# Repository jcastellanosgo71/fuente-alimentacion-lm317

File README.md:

# Fuente de Alimentación Lineal Regulable - v1.0

## 📌 Descripción General
Diseño de hardware y PCB para una **Fuente de Alimentación Lineal Regulable v1.0** basada en el regulador lineal ajustable **LM317**. El circuito convierte una entrada de voltaje continuo/alterno en una salida regulada ajustable ($V_{DD}$) mediante potenciómetro manual.

---

## 🛠️ Especificaciones y Funcionamiento
- **Entrada y Rectificación:** Bornera $J_1$ a la entrada con puente rectificador de onda completa (4x diodos 1N4004 $D_1-D_4$).
- **Filtrado Principal:** Capacitores electrolíticos en paralelo ($C_1, C_2$ de $2200\,\mu\text{F} / 50\,\text{V}$) para minimizar el rizado en $V_{CC}$.
- **Regulación y Ajuste:** Regulador lineal LM317 ($U_1$) en encapsulado TO-220, ajustado mediante potenciómetro de $5\,\text{k}\Omega$ ($RV_1$) y resistencia $R_2$.
- **Protección y Estabilidad:** Diodos de protección $D_6, D_7$ (1N4004), capacitor de desacople de ajuste $C_3$ ($33\,\mu\text{F}$) y capacitor de salida $C_4$ ($1\,\mu\text{F}$ Tántalo).
- **Salidas y Monitor:** Bornera principal $J_4$, salidas auxiliares $J_2, J_3$ y LED indicador $D_5$.
- **Diseño PCB:** Placa de 2 capas con plano de masa continuo ($GNDREF$).

---

## 📋 Lista de Componentes (BOM)

| Designador | Cantidad | Componente / Valor | Descripción |
| :--- | :--- | :--- | :--- |
| **U1** | 1 | LM317 | Regulador lineal ajustable (TO-220) |
| **D1, D2, D3, D4, D6, D7** | 6 | 1N4004 | Diodos rectificadores |
| **D5** | 1 | LED | Diodo emisor de luz 5mm |
| **C1, C2** | 2 | $2200\,\mu\text{F} / 50\,\text{V}$ | Condensadores electrolíticos radiales |
| **C3** | 1 | $33\,\mu\text{F} / 25\,\text{V}$ | Condensador electrolítico radial |
| **C4** | 1 | $1\,\mu\text{F} / 25\,\text{V}$ | Condensador de tántalo |
| **R1** | 1 | Resistencia (R) | Resistencia fija Through-Hole (LED indicador) |
| **R2** | 1 | $240\,\Omega$ / ¼ W | Resistencia de programación del LM317 (fija en v2.0) |
| **~~RV1~~** | — | ~~Potenciómetro $5\,\text{k}\Omega$~~ | **Retirado en v2.0** (sustituido por control digital) |
| **J1, J4** | 2 | Bornera 2 pines | Entradas/Salidas principales |
| **J2, J3** | 2 | Pin Header 1x02 | Salidas auxiliares $V_{CC}$ y $V_{DD}$ |
| **U2** | 1 | Opamp MCP6002 (o LM358) | Buffer/amplificador no inversor $G=2.15$ **(v2.0)** |
| **R3** | 1 | $10\,\text{k}\Omega$ / ¼ W | Resistencia del filtro RC **(v2.0)** |
| **C5** | 1 | $10\,\mu\text{F}$ / 16 V | Condensador del filtro RC **(v2.0)** |
| **R4** | 1 | $10\,\text{k}\Omega$ / ¼ W ($R_g$) | Resistencia de la red de ganancia **(v2.0)** |
| **R5** | 1 | $11.5\,\text{k}\Omega$ / ¼ W ($R_f'$) | Resistencia de realimentación de ganancia **(v2.0)** |
| **C6** | 1 | $100\,\text{nF}$ | Desacople de alimentación del opamp **(v2.0)** |
| **J5** | 1 | Pin Header 1x03 | Header de control Arduino: `PWM_IN`, `GND`, `VCC_OPAMP` (desde la placa, **no** del Arduino) **(v2.0)** |
| **HS1** | 1 | Disipador TO-220 $R_{th(SA)}\le 5\,^\circ\text{C/W}$ + pasta térmica | **Disipador por defecto** del LM317 (seguro a $0.5\,\text{A}$) **(v2.0)** |

> 📝 **Nota v2.0:** el potenciómetro $RV_1$ **se retira** y $R_2$ **pasa a valor fijo $240\,\Omega$**. Los componentes marcados **(v2.0)** son la etapa de control digital añadida. Ver [Control Digital v2.0](#-control-digital-v20).

---

## 🤖 Control Digital v2.0
En la **v2.0** se elimina el ajuste manual con potenciómetro ($RV_1$) y el voltaje de salida pasa a controlarse con un **Arduino estándar** (Uno/Nano), **sin perder la naturaleza de electrónica de potencia**: el elemento que entrega la potencia a la carga sigue siendo el regulador **lineal LM317** con rectificación por diodos a la entrada. El Arduino solo aporta una **consigna analógica de bajo nivel**.

El lazo de control es **PWM → RC → opamp → nodo ADJ**:

$$\text{PWM (0–5 V)} \;\rightarrow\; \text{Filtro RC} \;\rightarrow\; \text{Opamp no inversor } (G=2.15) \;\rightarrow\; \text{nodo ADJ del LM317}$$

1. **PWM:** un pin del Arduino genera una onda de $0\text{–}5\,\text{V}$ con ciclo de trabajo $D$ programable.
2. **Filtro RC** ($R_3=10\,\text{k}\Omega$, $C_5=10\,\mu\text{F}$, $f_c\approx 1.59\,\text{Hz}$): convierte el PWM en una tensión DC limpia $V_{rc}\in[0,5]\,\text{V}$.
3. **Opamp no inversor** ($R_g=10\,\text{k}\Omega$, $R_f'=11.5\,\text{k}\Omega$): amplifica a $0\text{–}10.75\,\text{V}$ y **aísla** el Arduino (lógica $5\,\text{V}$) del nodo ADJ, que puede superar los $10\,\text{V}$.
4. **Nodo ADJ:** como el LM317 mantiene $1.25\,\text{V}$ entre $V_O$ y ADJ, controlar el nodo ADJ controla la salida: $V_{out}=V_{ADJ}+1.25\,\text{V}$.

Relación consigna → salida (rango $1.25\,\text{V}$ a $\approx 12\,\text{V}$):

$$V_{out} = 10.75\cdot D + 1.25\,\text{V}\qquad D\in[0,1]$$

El PWM es de **8 bits** (256 niveles), por lo que la salida se cuantiza en pasos de $\approx 42\,\text{mV}$ ($10.75\,\text{V}/255$): es el límite de precisión frente al ajuste continuo del potenciómetro de la v1.0.

> 🚫 **Alimentación del opamp:** el opamp ($U_2$) se alimenta **desde la placa** ($V_{CC}\approx 18\,\text{V}$) o un riel auxiliar externo de $12\text{–}15\,\text{V}$, **NUNCA desde el Arduino**. El pin `VCC_OPAMP` de $J_5$ trae esa alimentación de placa/riel auxiliar, no del Arduino (que solo da $5\,\text{V}$, insuficientes para los $\approx 10.75\,\text{V}$ de salida del opamp).
>
> ⚠️ **Masa común:** el $GNDREF$ de la placa y la masa del Arduino deben unirse (vía $J_5$, pin 2). El Arduino se alimenta **aparte** y **solo** comparte GND y la señal PWM con la placa.
>
> 🌡️ **Térmica (configuración segura por defecto):** el LM317 es lineal y el peor caso térmico es a $V_{out}$ mínima ($\approx 8.4\,\text{W}$ a $0.5\,\text{A}$). La v2.0 **fija un disipador $HS_1$ con $R_{th(SA)}\le 5\,^\circ\text{C/W}$** ($T_j\approx 100\,^\circ\text{C}$, dentro de margen). Alternativa segura: disipador pequeño con **corriente limitada a $I_{load}\le 0.3\,\text{A}$**. Ver cálculo en el [documento de diseño §7.1](docs/DISENO_V2_CONTROL_DIGITAL.md).

**Documentación de la v2.0:**
- 📐 Diseño y cálculos (filtro RC, ganancia, $R_2$, térmica): [`docs/DISENO_V2_CONTROL_DIGITAL.md`](docs/DISENO_V2_CONTROL_DIGITAL.md)
- 🛠️ Guía de modificación en KiCad (esquemático + PCB): [`docs/GUIA_MODIFICACION_KICAD.md`](docs/GUIA_MODIFICACION_KICAD.md)
- 💻 Firmware del Arduino: [`firmware/control_lm317.ino`](firmware/control_lm317.ino)

---

## 🚀 Roadmap (Versión 2.0 - Digitalización)
- [x] Reemplazar potenciómetro analógico ($RV_1$) por control digital (PWM → RC → opamp → nodo ADJ). **Implementado en v2.0.**
- [ ] Control por microcontrolador (ESP32 / STM32 / ATmega328P).
- [ ] Lectura de voltaje y corriente en tiempo real con sensor INA219.
- [ ] Integración de pantalla OLED / LCD I2C.
- [ ] Protección por sobrecorriente implementada por software/hardware.

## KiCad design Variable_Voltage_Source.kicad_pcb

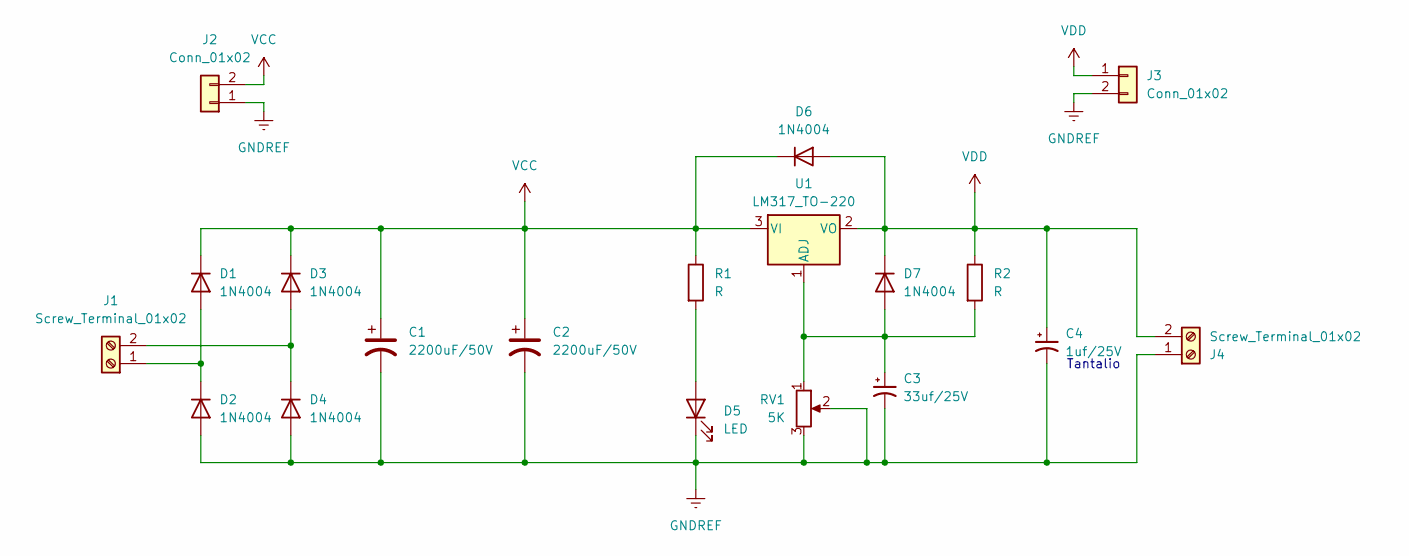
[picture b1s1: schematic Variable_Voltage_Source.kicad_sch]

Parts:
C1, C2: 2200uF/50V; CP_Radial_D16.0mm_P7.50mm
C3: 33uf/25V; CP_Radial_D6.3mm_P2.50mm
C4: 1uf/25V; C_Disc_D5.0mm_W2.5mm_P2.50mm
D1, D2, D3, D4, D6, D7: 1N4004; D_DO-41_SOD81_P10.16mm_Horizontal
D5: LED; LED_D5.0mm
J1, J4: Screw_Terminal_01x02; TerminalBlock_MaiXu_MX126-5.0-02P_1x02_P5.00mm
J2, J3: Conn_01x02; PinHeader_1x02_P2.54mm_Vertical
R1, R2: R; R_Axial_DIN0207_L6.3mm_D2.5mm_P10.16mm_Horizontal
RV1: 5K; Potentiometer_Alps_RK09Y11_Single_Horizontal
U1: LM317_TO-220; TO-220-3_Vertical

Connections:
GNDREF: C1.2, C2.2, C3.2, C4.2, D2.2 (A), D4.2 (A), D5.1 (K), J2.1, J3.2, J4.1, RV1.2, RV1.3
unnamed: D1.2 (A), D2.1 (K), J1.1
unnamed: D3.2 (A), D4.1 (K), J1.2
unnamed: D5.2 (A), R1.2
unnamed: C3.1, D7.2 (A), R2.2, RV1.1, U1.1 (ADJ)
VCC: C1.1, C2.1, D1.1 (K), D3.1 (K), D6.1 (K), J2.2, R1.1, U1.3 (VI)
VDD: C4.1, D6.2 (A), D7.1 (K), J3.1, J4.2, R2.1, U1.2 (VO)

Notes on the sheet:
Tantalio

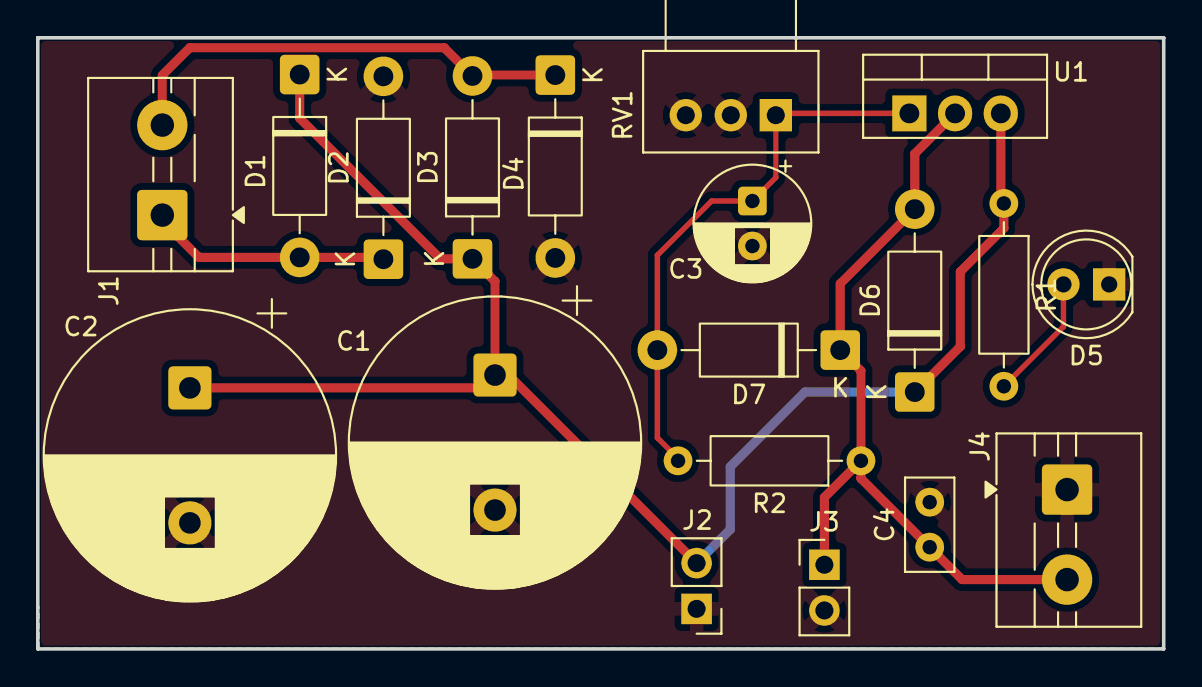
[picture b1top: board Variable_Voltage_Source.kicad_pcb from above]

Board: 2 copper layers, 62.6 x 34.0 mm, 19 parts (0 on the bottom side), 7 nets.
